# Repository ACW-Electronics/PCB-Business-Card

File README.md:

# PCB-Business-Card
Making an NFC PCB Business Card

NOTE FOR REVIEWER:
I do not have firmware since this is going to be written for nfc via my phone. It will link to my personal website, andrewcwong.com, but there is no firmware I am writing. Also, the actual BOM is the one called PCB Busines Card-bom.csv. The other file was for JLCPCB. I'm doing PCBA since it'd be cheaper than buying the components individually and soldering them on. Also, sorry for the file dump, not sure what the autochecker was missing so I threw on a bunch of files till it worked

I'm making this so that I have a flashier business card as an electrical engineering student that is memorable and let's me share my portfolio/resume.

Schematic:

PCB Layout:

3D Viewer:

BOM:
| Name | Purpose | Quantity | Total Cost (USD) | Link | Distributor |
| :--- | :--- | :---: | :---: | :--- | :--- |
| PCBA | PCB with components from JLCPCB | 1 | $19.63 | [Link](https://cart.jlcpcb.com/shopcart/cart) | JLCPCB |

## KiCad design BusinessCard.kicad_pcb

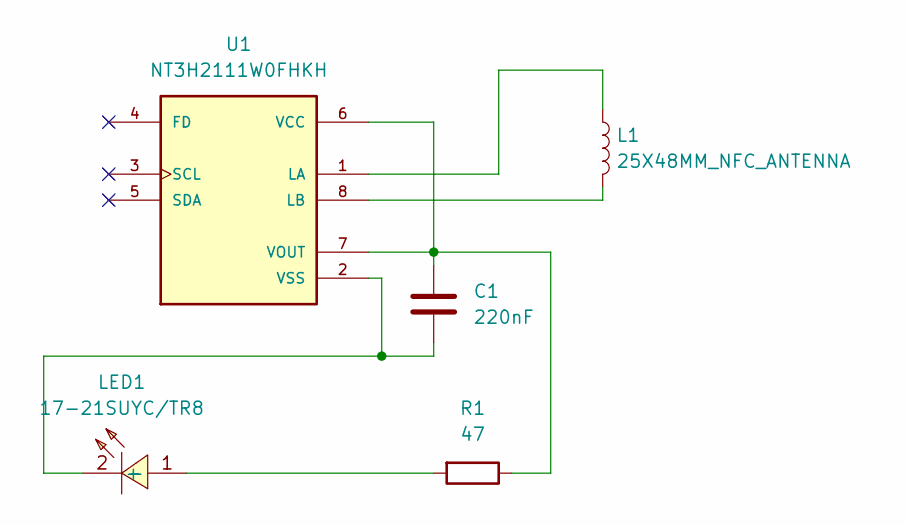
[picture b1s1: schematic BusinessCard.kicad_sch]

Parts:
C1: 220nF; C_0603_1608Metric
L1: 25X48MM_NFC_ANTENNA
LED1: 17-21SUYC/TR8; LED0805-R-RD; MPN KT-0805黄灯; LCSC Part C2296
R1: 47; R_0603_1608Metric
U1: NT3H2111W0FHKH; QFN8P50_160X160X50L40X20N

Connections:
unnamed: LED1.1 (+), R1.2
unnamed: C1.2, LED1.2 (-), U1.2 (VSS)
unnamed: L1.1, U1.1 (LA)
unnamed: L1.2, U1.8 (LB)
unnamed: C1.1, R1.1, U1.6 (VCC), U1.7 (VOUT)

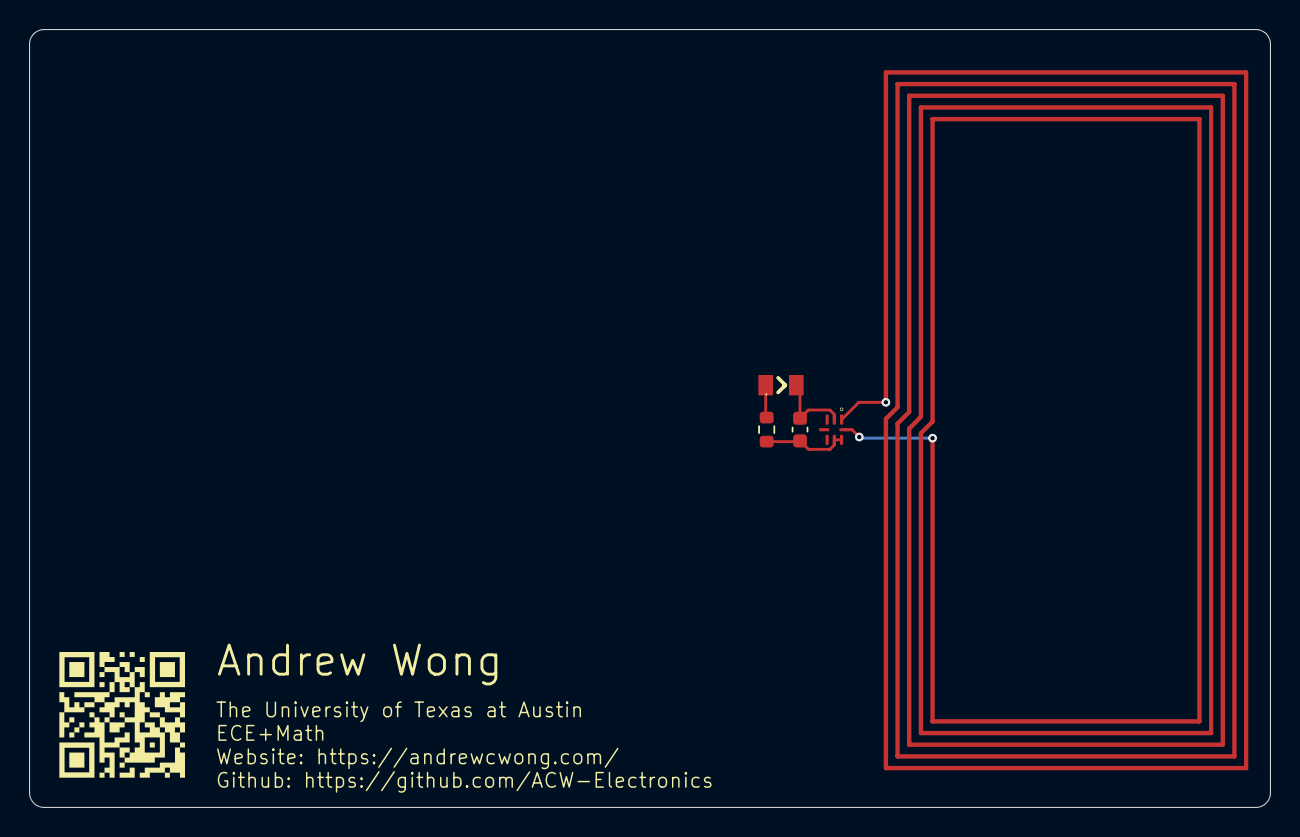
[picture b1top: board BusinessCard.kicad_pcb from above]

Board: 2 copper layers, 85.1 x 53.3 mm, 5 parts (0 on the bottom side), 5 nets.

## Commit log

2026-04-27 Enhance README with project details and visuals
    Added project description and images for schematic, PCB layout, and 3D viewer.
2026-04-27 3d-Model + BOM + GBR/DRL Files
2026-04-27 Add BOM section to README
    Added a Bill of Materials (BOM) section with details.
2026-04-27 Add reviewer note and clarify firmware information
    Added a note for reviewers regarding firmware and BOM.
2026-04-27 Update README with reviewer note clarification
2026-04-27 Update README with PCBA details and context
    Added additional context regarding PCBA and file management.
